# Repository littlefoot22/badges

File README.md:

# Char badge

https://twitter.com/littlefoot20_2/status/1213898357694971907/photo/1
https://twitter.com/littlefoot20_2/status/1128459009160359936/photo/1

# Dolly badge

https://twitter.com/littlefoot20_2/status/1213898357694971907/photo/2
https://twitter.com/littlefoot20_2/status/1159295666331553794?s=21

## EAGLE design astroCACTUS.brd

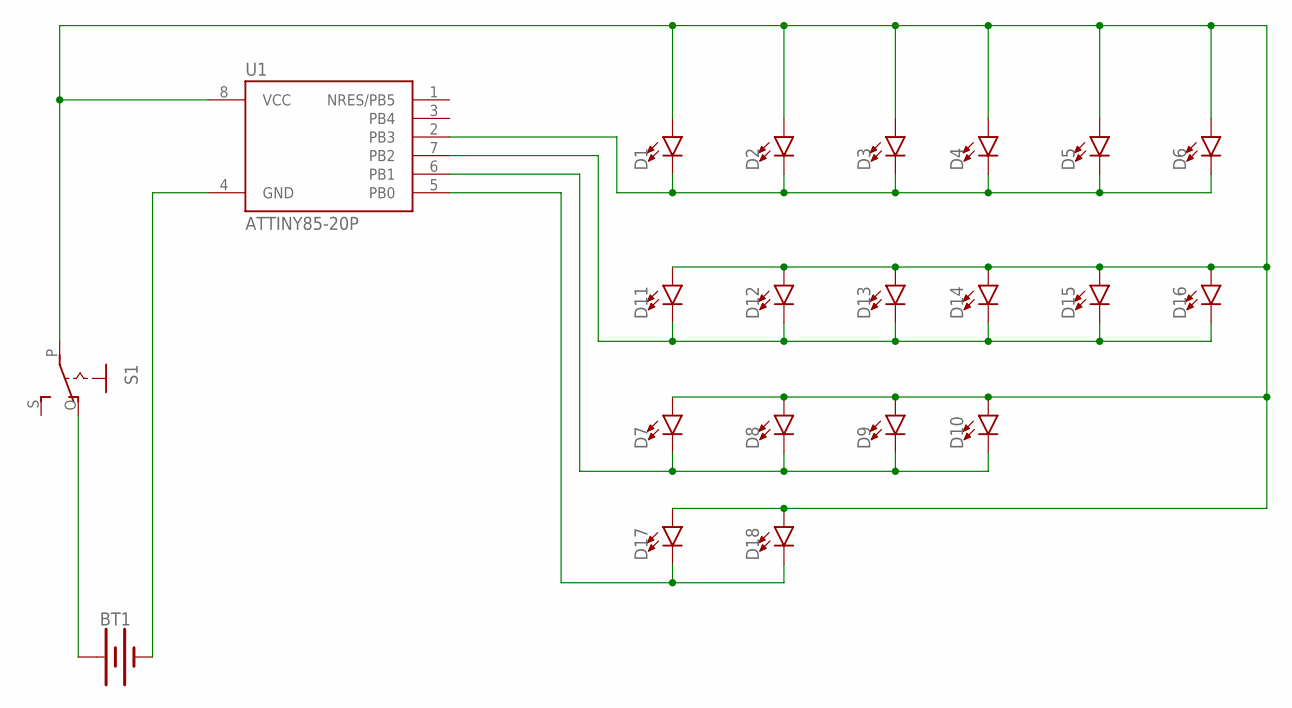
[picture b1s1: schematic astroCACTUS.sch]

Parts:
BT1: BATTERY-20MM_PTH; BATTCOM_20MM_PTH
D1, D2, D3, D4, D5, D6, D7, D8, D9, D10, D11, D12, D13, D14, D15, D16, D17, D18: LED3MM; LED_3MM
S1: EG1218S; EG1218
U1: ATTINY85-20P; PDIP08_300MIL

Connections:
unnamed: D1.K (C), D2.K (C), D3.K (C), D4.K (C), D5.K (C), D6.K (C), U1.2 (PB3)
unnamed: BT1.1 (+), S1.O
unnamed: D11.K (C), D12.K (C), D13.K (C), D14.K (C), D15.K (C), D16.K (C), U1.7 (PB2)
unnamed: D7.K (C), D8.K (C), D9.K (C), D10.K (C), U1.6 (PB1)
unnamed: BT1.2 (-), U1.4 (GND)
unnamed: D17.K (C), D18.K (C), U1.5 (PB0)
unnamed: D1.A, D2.A, D3.A, D4.A, D5.A, D6.A, D7.A, D8.A, D9.A, D10.A, D11.A, D12.A, D13.A, D14.A, D15.A, D16.A, D17.A, D18.A, S1.P, U1.8 (VCC)

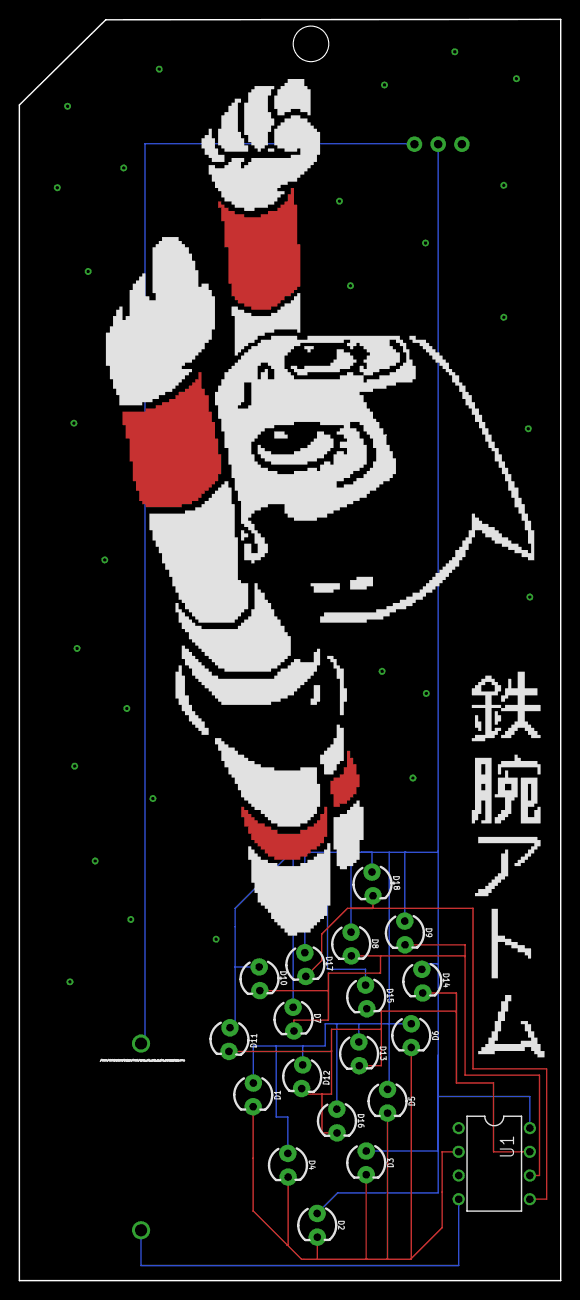
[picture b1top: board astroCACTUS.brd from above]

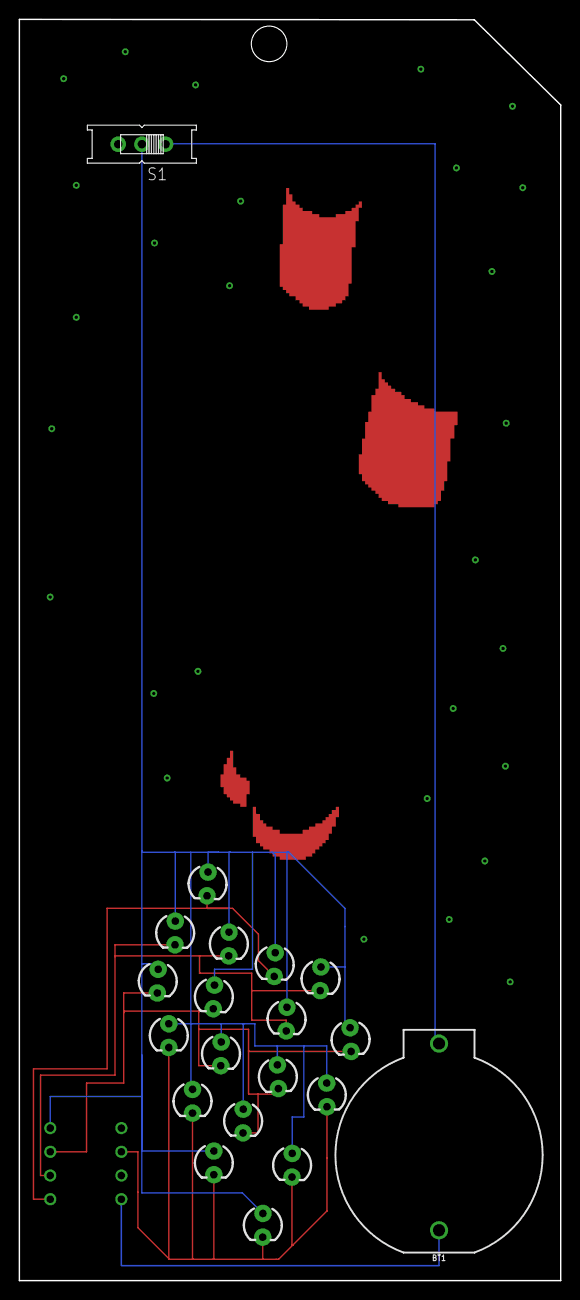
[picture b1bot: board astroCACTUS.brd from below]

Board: 2 copper layers, 58.0 x 135.1 mm, 21 parts (2 on the bottom side), 7 nets.

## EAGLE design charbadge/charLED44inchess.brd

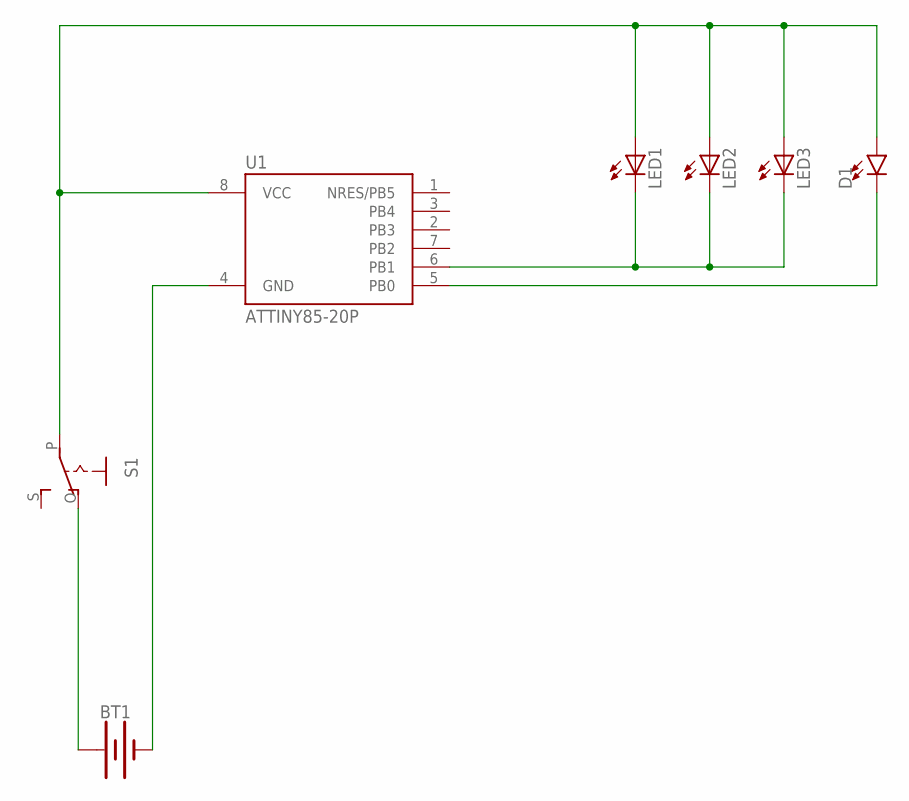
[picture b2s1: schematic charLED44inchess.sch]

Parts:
BT1: BATTERY-20MM_PTH; BATTCOM_20MM_PTH
D1: LED3MM; LED_3MM
LED1, LED2, LED3: LED5MM
S1: EG1218S; EG1218
U1: ATTINY85-20P; PDIP08_300MIL

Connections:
unnamed: LED1.K (C), LED2.K (C), LED3.K (C), U1.6 (PB1)
unnamed: BT1.1 (+), S1.O
unnamed: D1.K (C), U1.5 (PB0)
unnamed: BT1.2 (-), U1.4 (GND)
unnamed: D1.A, LED1.A, LED2.A, LED3.A, S1.P, U1.8 (VCC)

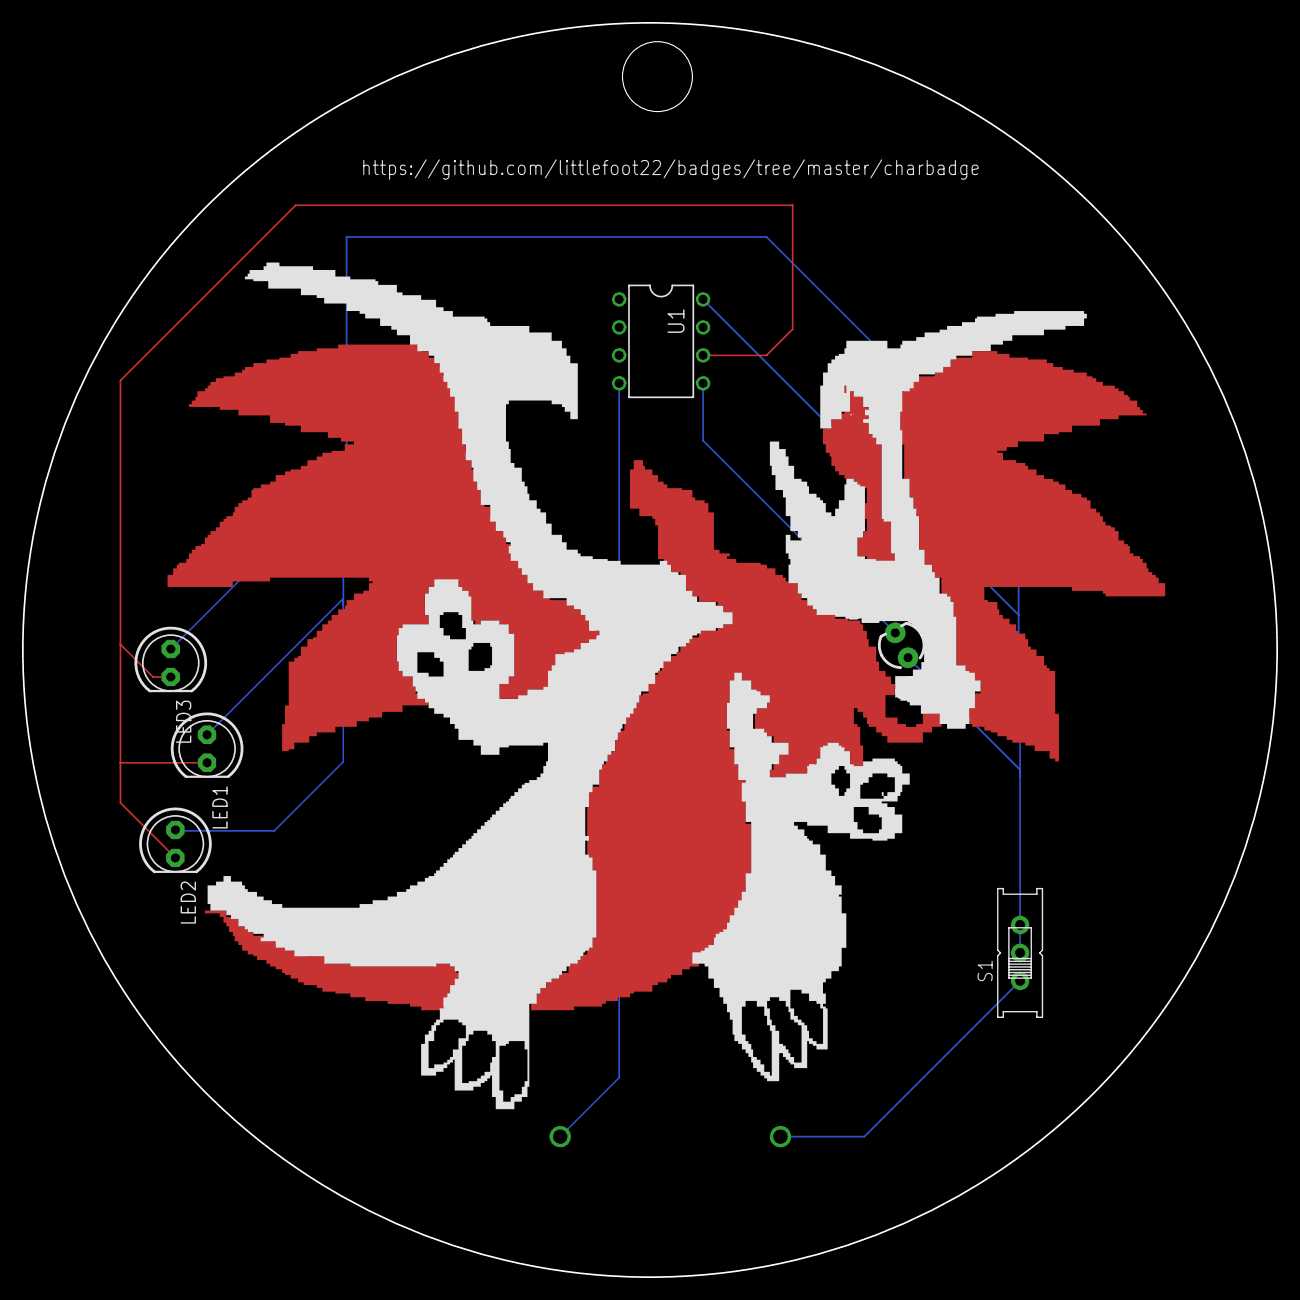
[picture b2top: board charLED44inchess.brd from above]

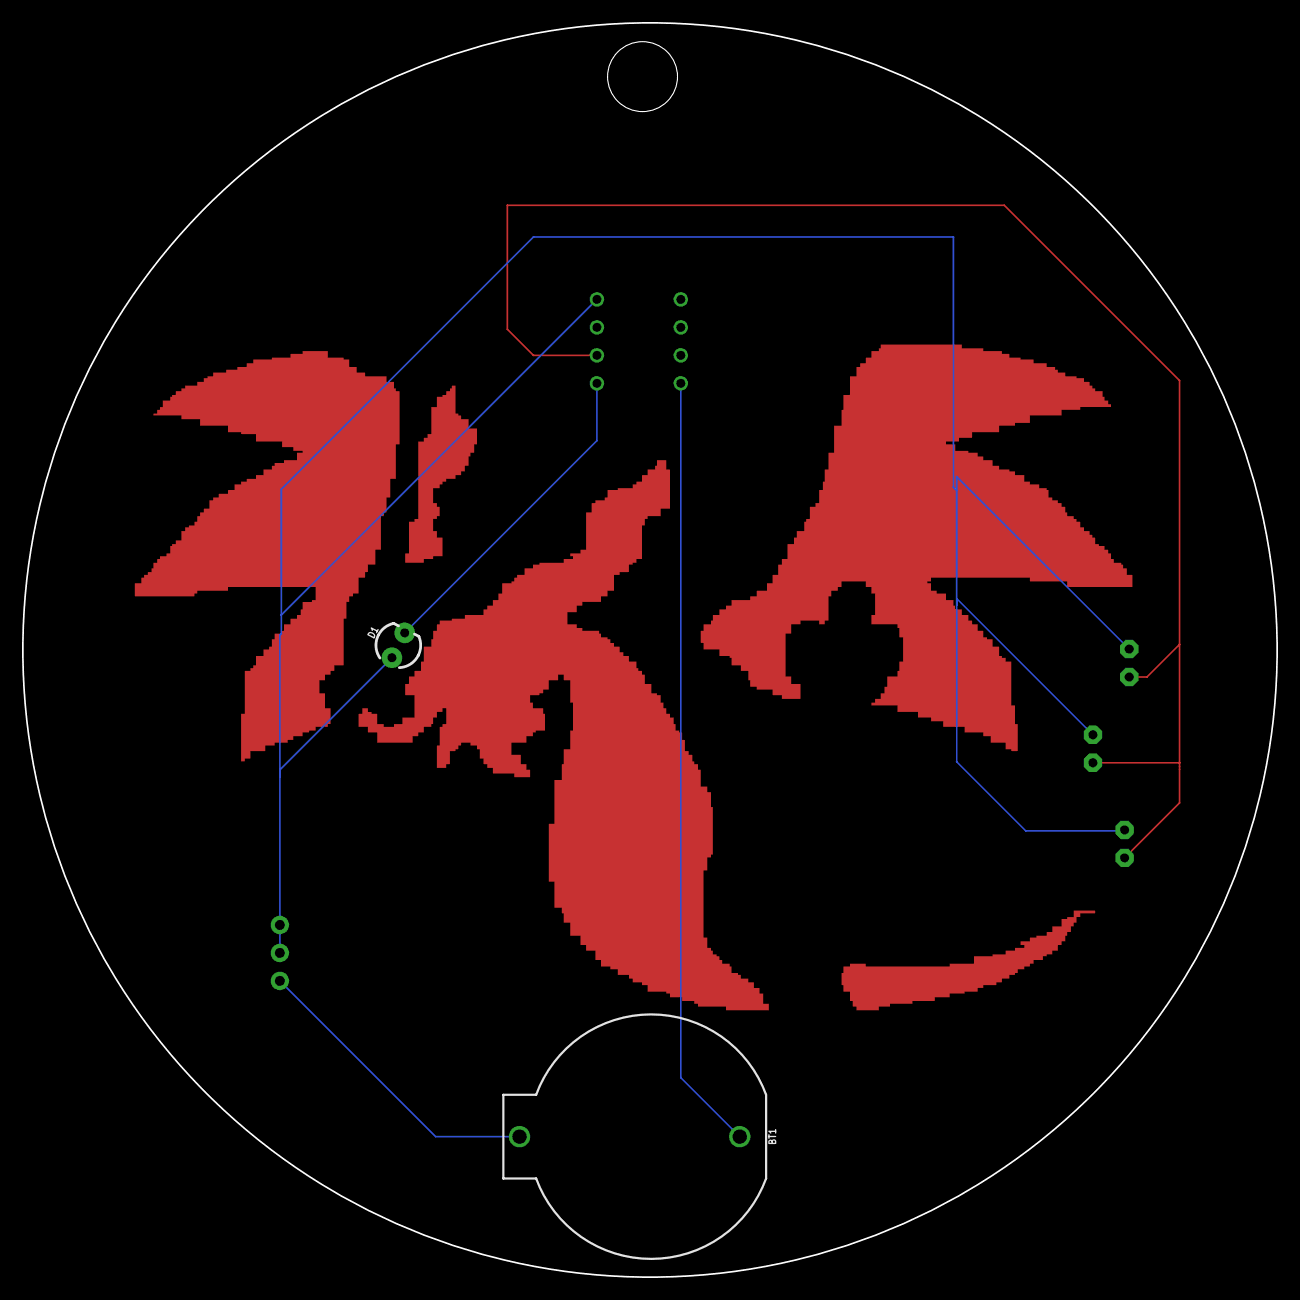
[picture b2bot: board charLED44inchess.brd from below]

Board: 2 copper layers, 113.9 x 113.9 mm, 7 parts (2 on the bottom side), 5 nets.

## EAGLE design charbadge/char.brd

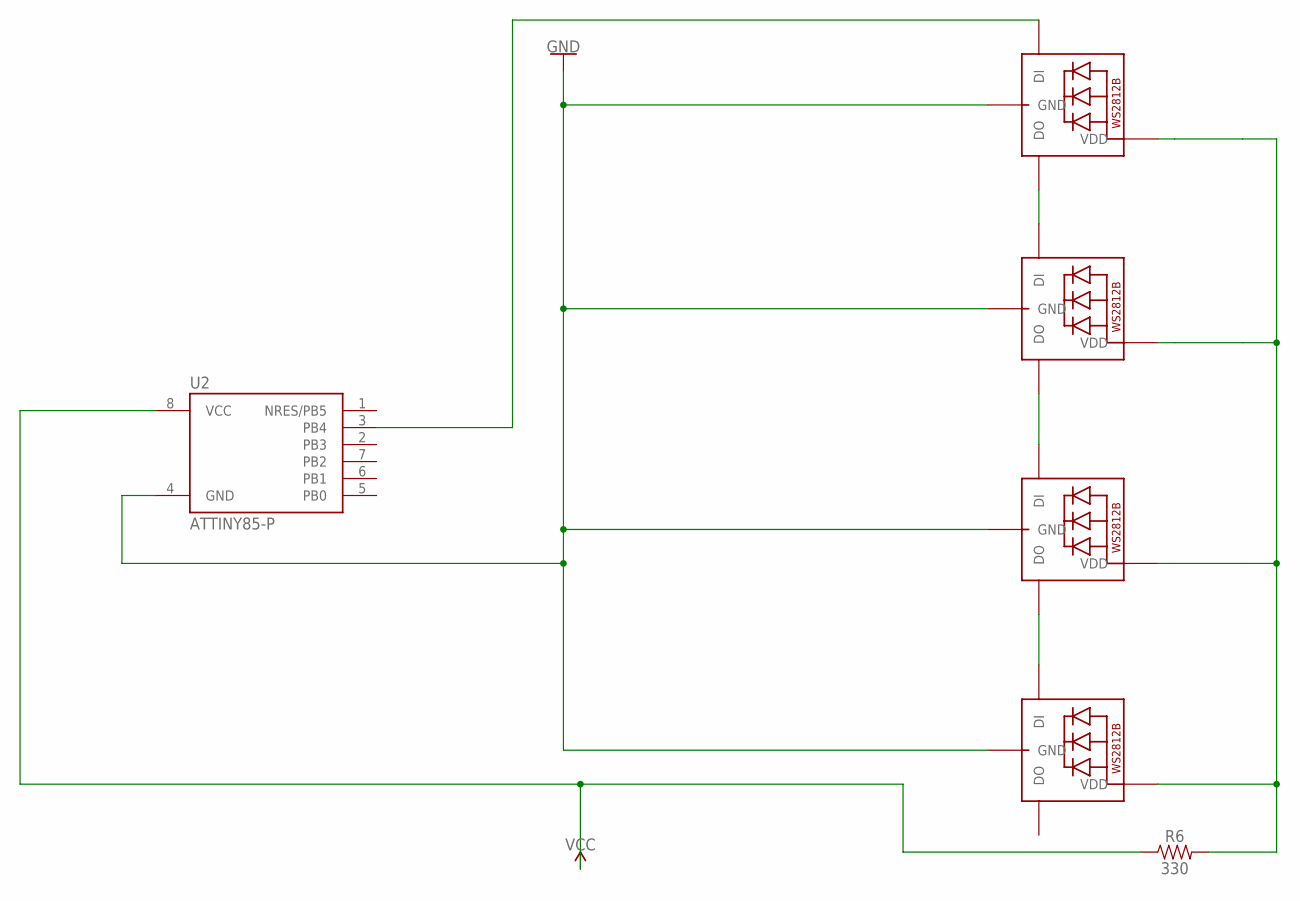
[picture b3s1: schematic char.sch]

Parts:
R6: 330; AXIAL-0.3
U2: ATTINY85-P; PDIP08_300MIL
U$1, U$2, U$3, U$4: THROHOLE; LED5MMRGB

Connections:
GND: U2.4 (GND), U$1.2 (GND), U$2.2 (GND), U$3.2 (GND), U$4.2 (GND)
unnamed: U2.3 (PB4), U$4.1 (DI)
unnamed: U$1.1 (DI), U$4.4 (DO)
unnamed: U$1.4 (DO), U$2.1 (DI)
unnamed: U$2.4 (DO), U$3.1 (DI)
unnamed: R6.P$2 (2), U$1.3 (VDD), U$2.3 (VDD), U$3.3 (VDD), U$4.3 (VDD)
VCC: R6.P$1 (1), U2.8 (VCC)

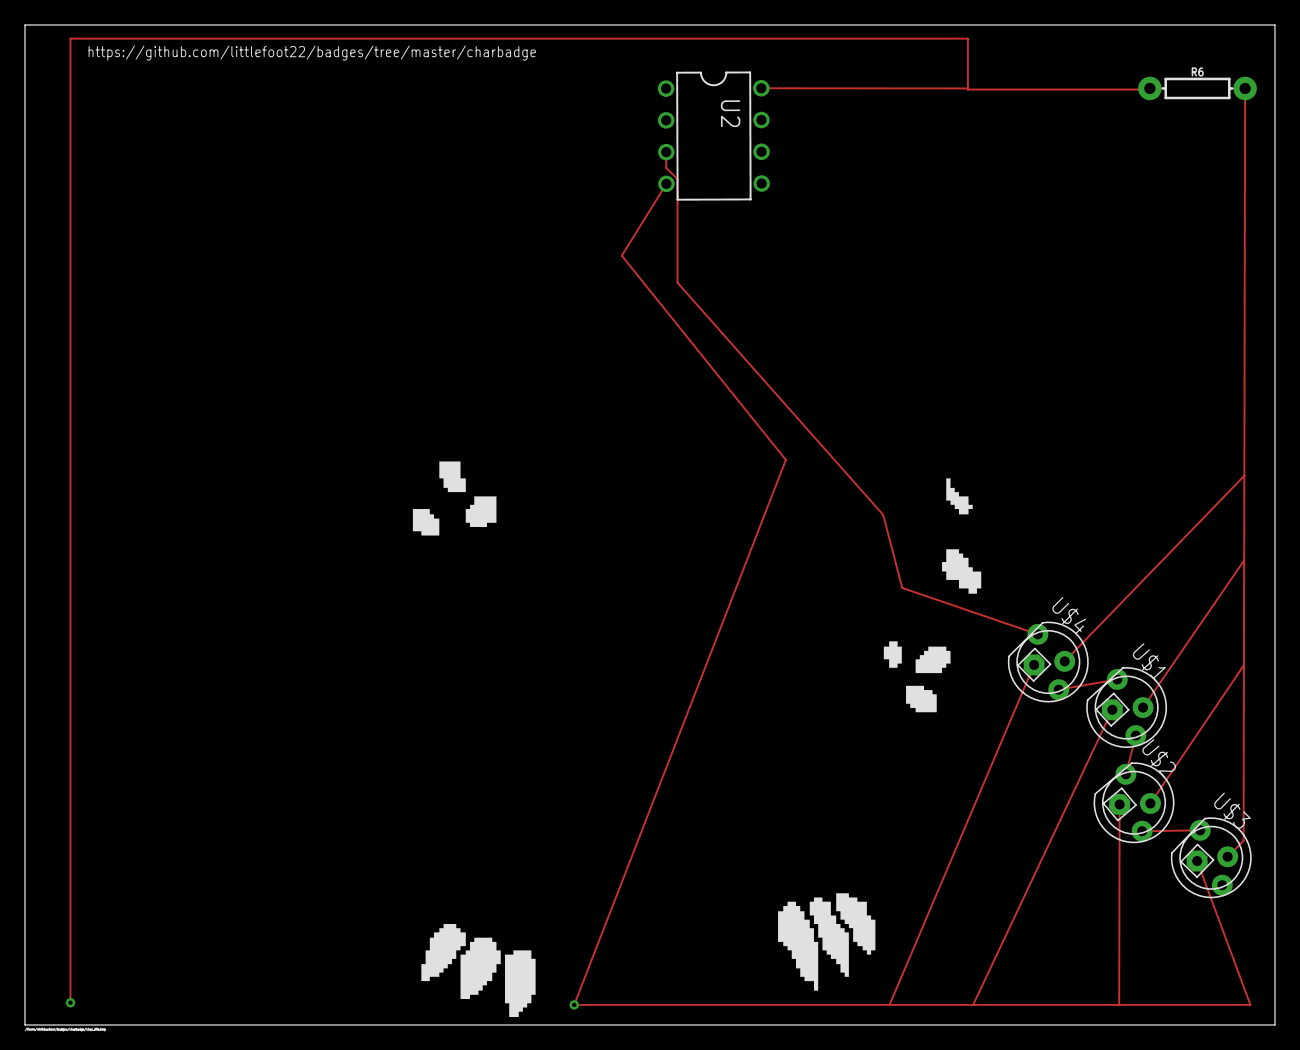
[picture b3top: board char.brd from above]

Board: 2 copper layers, 100.0 x 80.0 mm, 6 parts (0 on the bottom side), 7 nets.

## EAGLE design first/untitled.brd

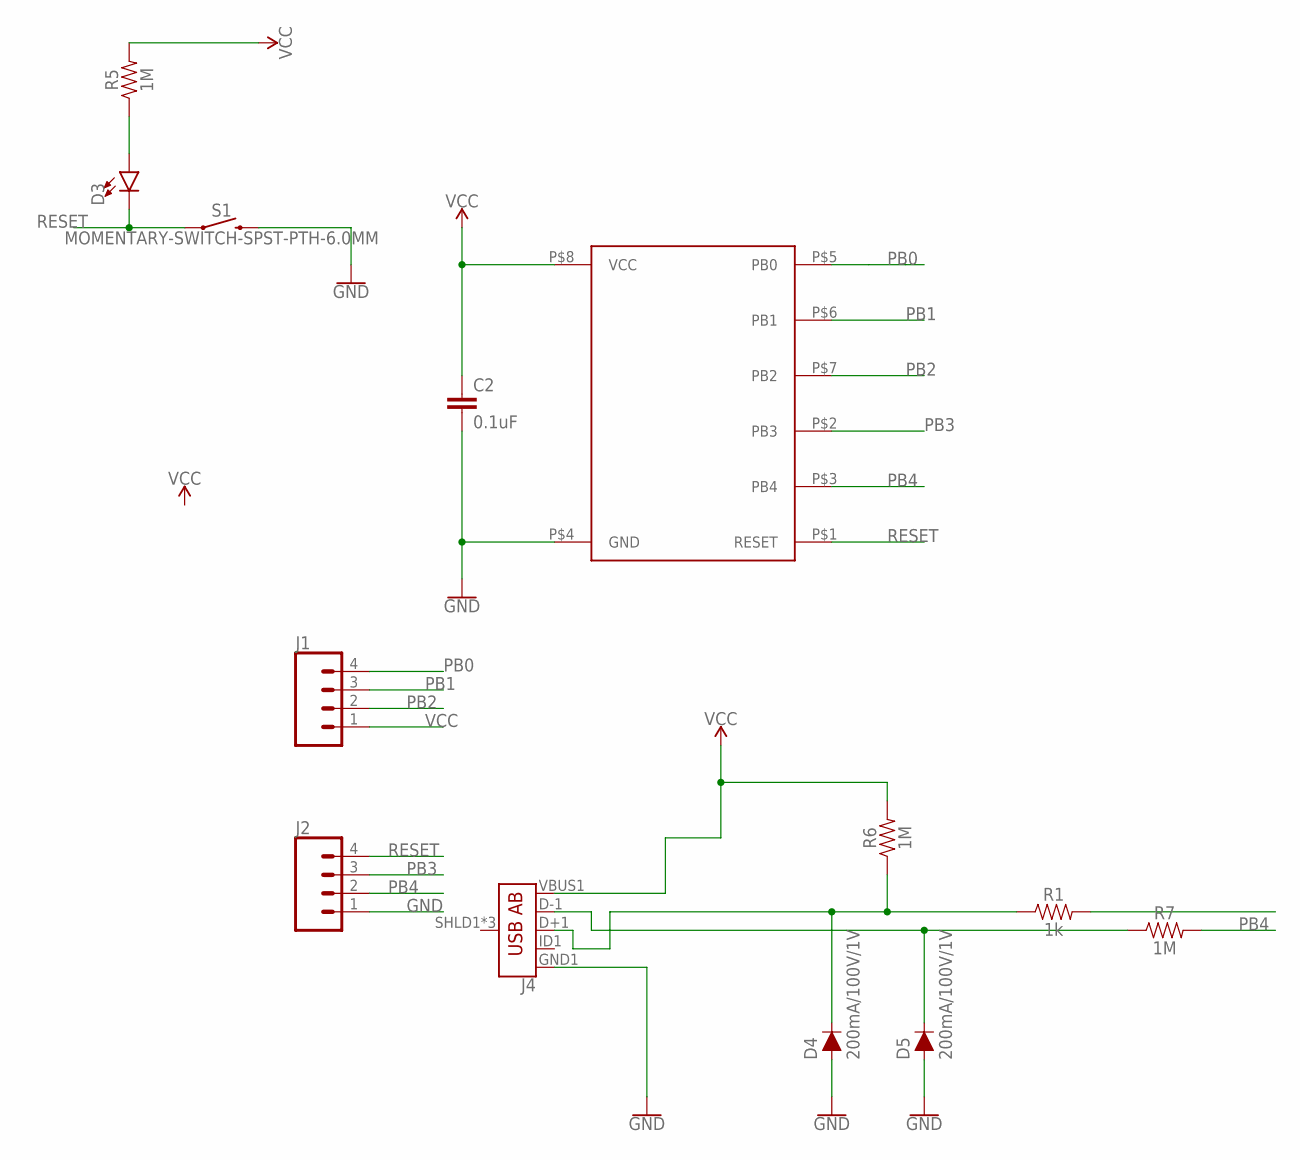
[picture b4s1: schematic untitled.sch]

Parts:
C2: 0.1uF; CAP-PTH-SMALL-KIT
D3: LED-3MM-NO_SILK; LED_3MM-NS
D4, D5: 200mA/100V/1V; DIODE-1N4148
J1, J2: CONN_04; 1X04
J4: USB_AB_SMT; USB-AB-MICRO-SMD
R1: 1k; AXIAL-0.3
R5, R6, R7: 1M; AXIAL-0.3
S1: MOMENTARY-SWITCH-SPST-PTH-6.0MM; TACTILE_SWITCH_PTH_6.0MM
U$2: ATINY85; DIP8

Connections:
GND: C2.2, D4.A, D5.A, J2.1, J4.GND1 (GND), S1.3 (2), U$2.P$4 (GND)
unnamed: D3.A, R5.P$1 (1)
unnamed: D5.C, J4.D-1 (D-), R7.P$1 (1)
unnamed: D4.C, J4.D+1 (D+), R1.P$1 (1), R6.P$1 (1)
PB0: J1.4, U$2.P$5 (PB0)
PB1: J1.3, U$2.P$6 (PB1)
PB2: J1.2, U$2.P$7 (PB2)
PB3: J2.3, R1.P$2 (2), U$2.P$2 (PB3)
PB4: J2.2, R7.P$2 (2), U$2.P$3 (PB4)
RESET: D3.K (C), J2.4, S1.1, U$2.P$1 (RESET)
VCC: C2.1, J1.1, J4.VBUS1 (VBUS), R5.P$2 (2), R6.P$2 (2), U$2.P$8 (VCC)

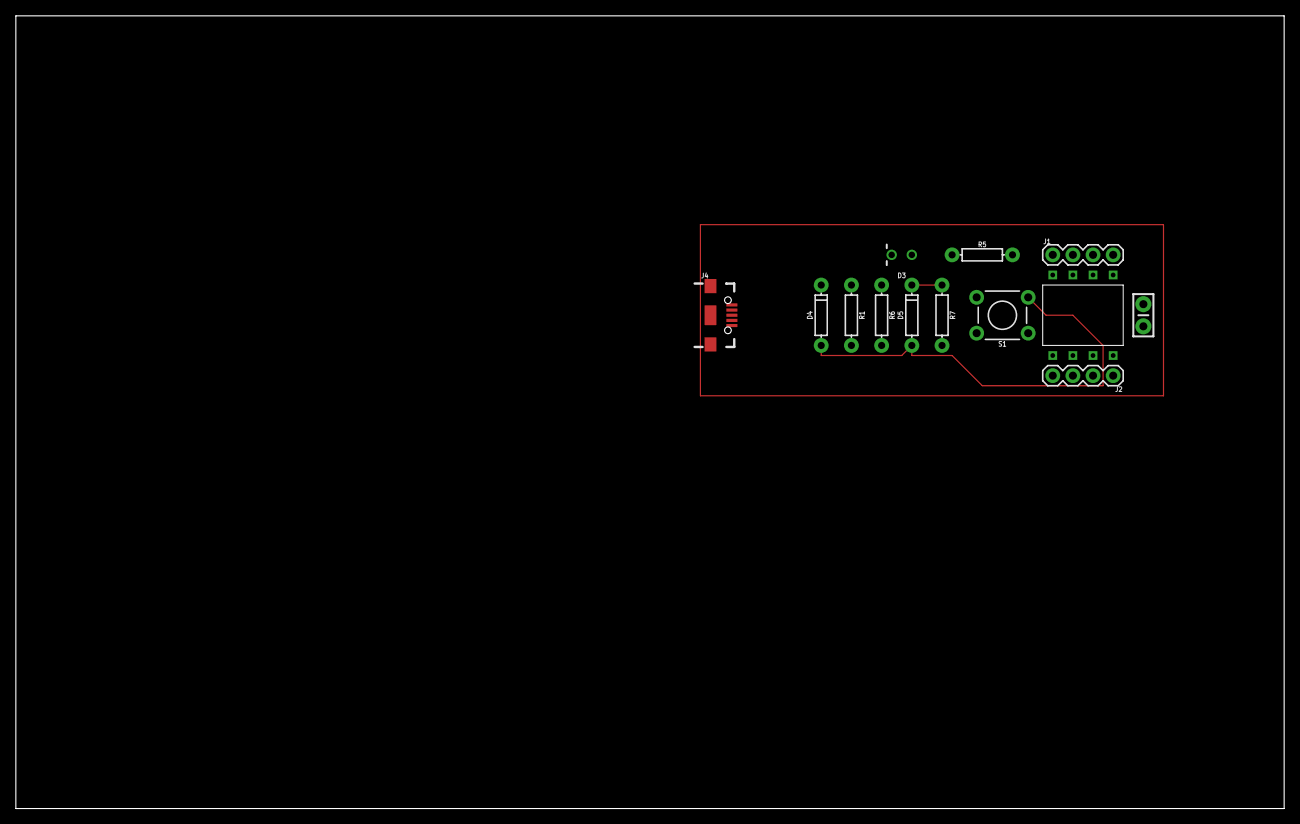
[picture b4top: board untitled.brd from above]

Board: 2 copper layers, 160.0 x 100.0 mm, 13 parts (0 on the bottom side), 11 nets.

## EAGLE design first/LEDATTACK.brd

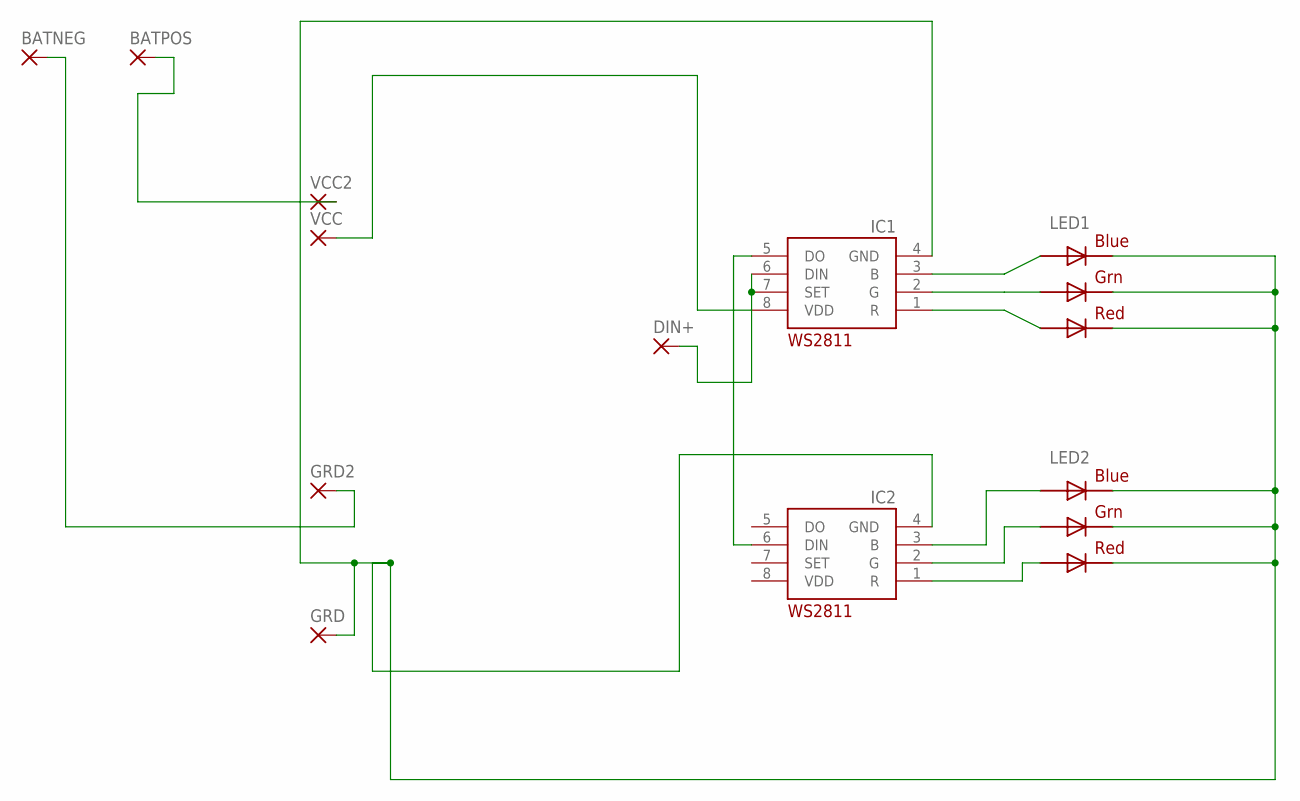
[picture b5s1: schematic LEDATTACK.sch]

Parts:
BATNEG: 1,6/0,8
BATPOS: 1,6/0,8
DIN+: 1,6/0,8
GRD, GRD2: 1,6/0,8
IC1, IC2: WS2811-SOP8; SO08-SKINNYPADS
LED1, LED2: RGBLED5050
VCC, VCC2: 1,6/0,8

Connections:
unnamed: IC1.3 (B), LED1.3 (BLUE_A)
unnamed: IC1.2 (G), LED1.1 (GREEN_A)
unnamed: IC1.1 (R), LED1.2 (RED_A)
unnamed: GRD.1, IC1.4 (GND), IC2.4 (GND), LED1.4 (BLUE_C), LED1.5 (RED_C), LED1.6 (GREEN_C), LED2.4 (BLUE_C), LED2.5 (RED_C), LED2.6 (GREEN_C)
unnamed: IC1.8 (VDD), VCC.1
unnamed: DIN+.1, IC1.6 (DIN), IC1.7 (SET)
unnamed: IC1.5 (DO), IC2.6 (DIN)
unnamed: IC2.1 (R), LED2.2 (RED_A)
unnamed: IC2.2 (G), LED2.1 (GREEN_A)
unnamed: IC2.3 (B), LED2.3 (BLUE_A)
unnamed: BATPOS.1, VCC2.1
unnamed: BATNEG.1, GRD2.1
VDD: IC2.8 (VDD)

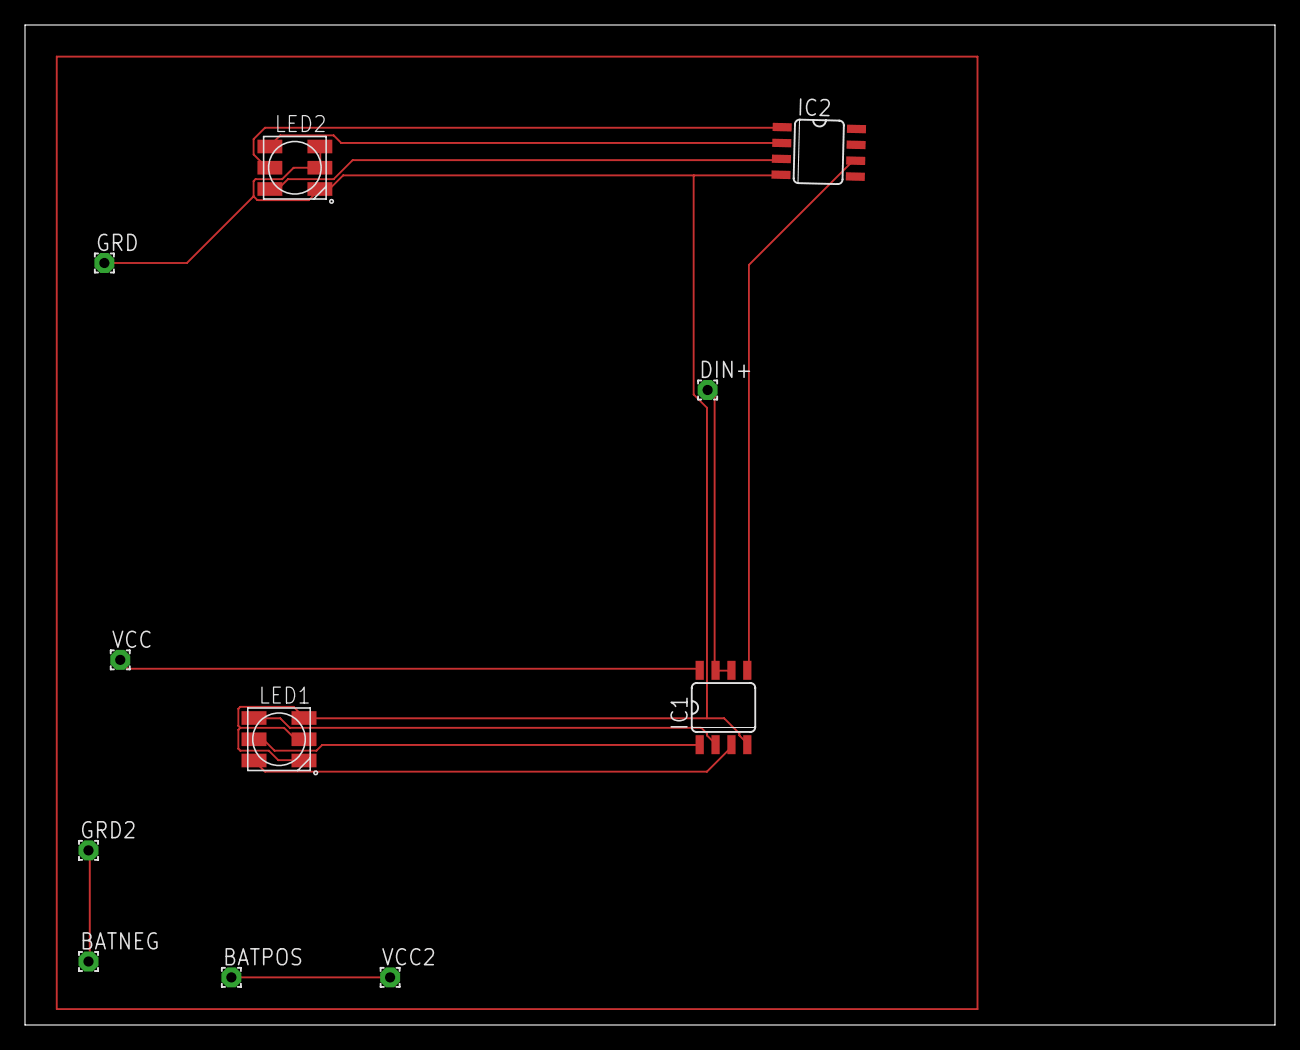
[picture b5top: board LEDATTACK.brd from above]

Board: 2 copper layers, 100.0 x 80.0 mm, 11 parts (0 on the bottom side), 12 nets.

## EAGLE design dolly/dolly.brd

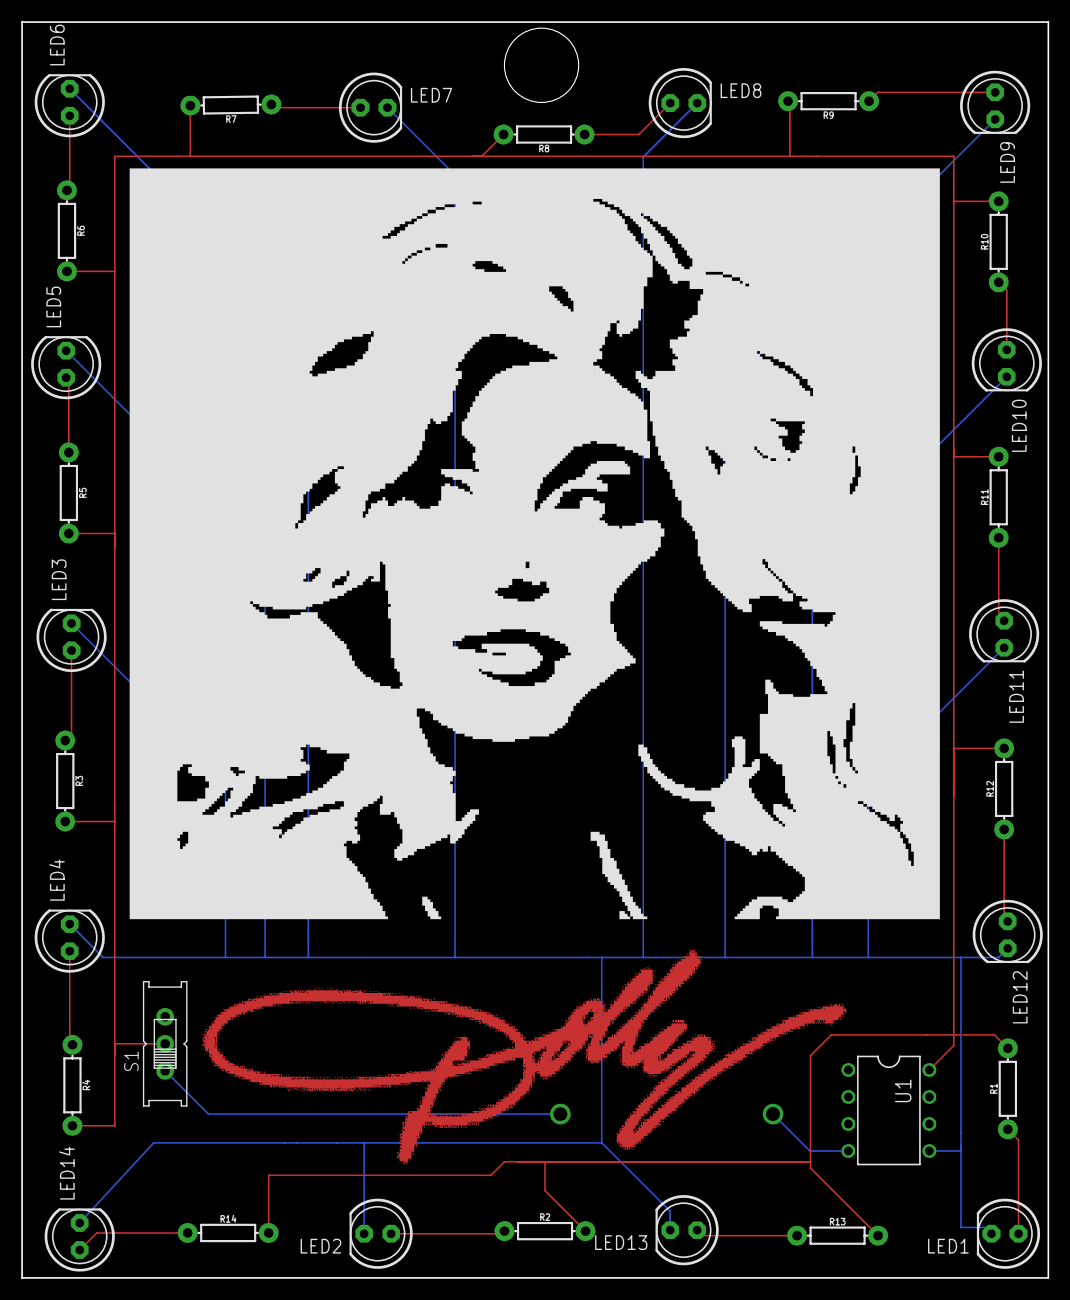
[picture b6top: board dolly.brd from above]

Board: 2 copper layers, 96.5 x 118.1 mm, 31 parts (1 on the bottom side), 18 nets.

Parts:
BT1: BATTCOM_20MM_PTH
LED1, LED2, LED3, LED4, LED5, LED6, LED7, LED8, LED9, LED10, LED11, LED12, LED13, LED14: LED5MM
R1, R2, R3, R4, R5, R6, R7, R8, R9, R10, R11, R12, R13, R14: 10k; AXIAL-0.3
S1: EG1218
U1: ATTINY85-20P; PDIP08_300MIL

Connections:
unnamed: LED1.A, R1.P$1
unnamed: BT1.1, S1.O
unnamed: LED3.A, R3.P$1
unnamed: LED1.K, LED2.K, LED3.K, LED4.K, LED5.K, LED6.K, LED7.K, LED8.K, LED9.K, LED10.K, LED11.K, LED12.K, LED13.K, LED14.K, U1.5
unnamed: BT1.2, U1.4
unnamed: R1.P$2, R2.P$2, R3.P$2, R4.P$2, R5.P$2, R6.P$2, R7.P$2, R8.P$2, R9.P$2, R10.P$2, R11.P$2, R12.P$2, R13.P$2, R14.P$2, S1.P, U1.8
unnamed: LED4.A, R4.P$1
unnamed: LED5.A, R5.P$1
unnamed: LED6.A, R6.P$1
unnamed: LED7.A, R7.P$1
unnamed: LED8.A, R8.P$1
unnamed: LED9.A, R9.P$1
unnamed: LED10.A, R10.P$1
unnamed: LED11.A, R11.P$1
unnamed: LED12.A, R12.P$1
unnamed: LED13.A, R13.P$1
unnamed: LED14.A, R14.P$1
unnamed: LED2.A, R2.P$1

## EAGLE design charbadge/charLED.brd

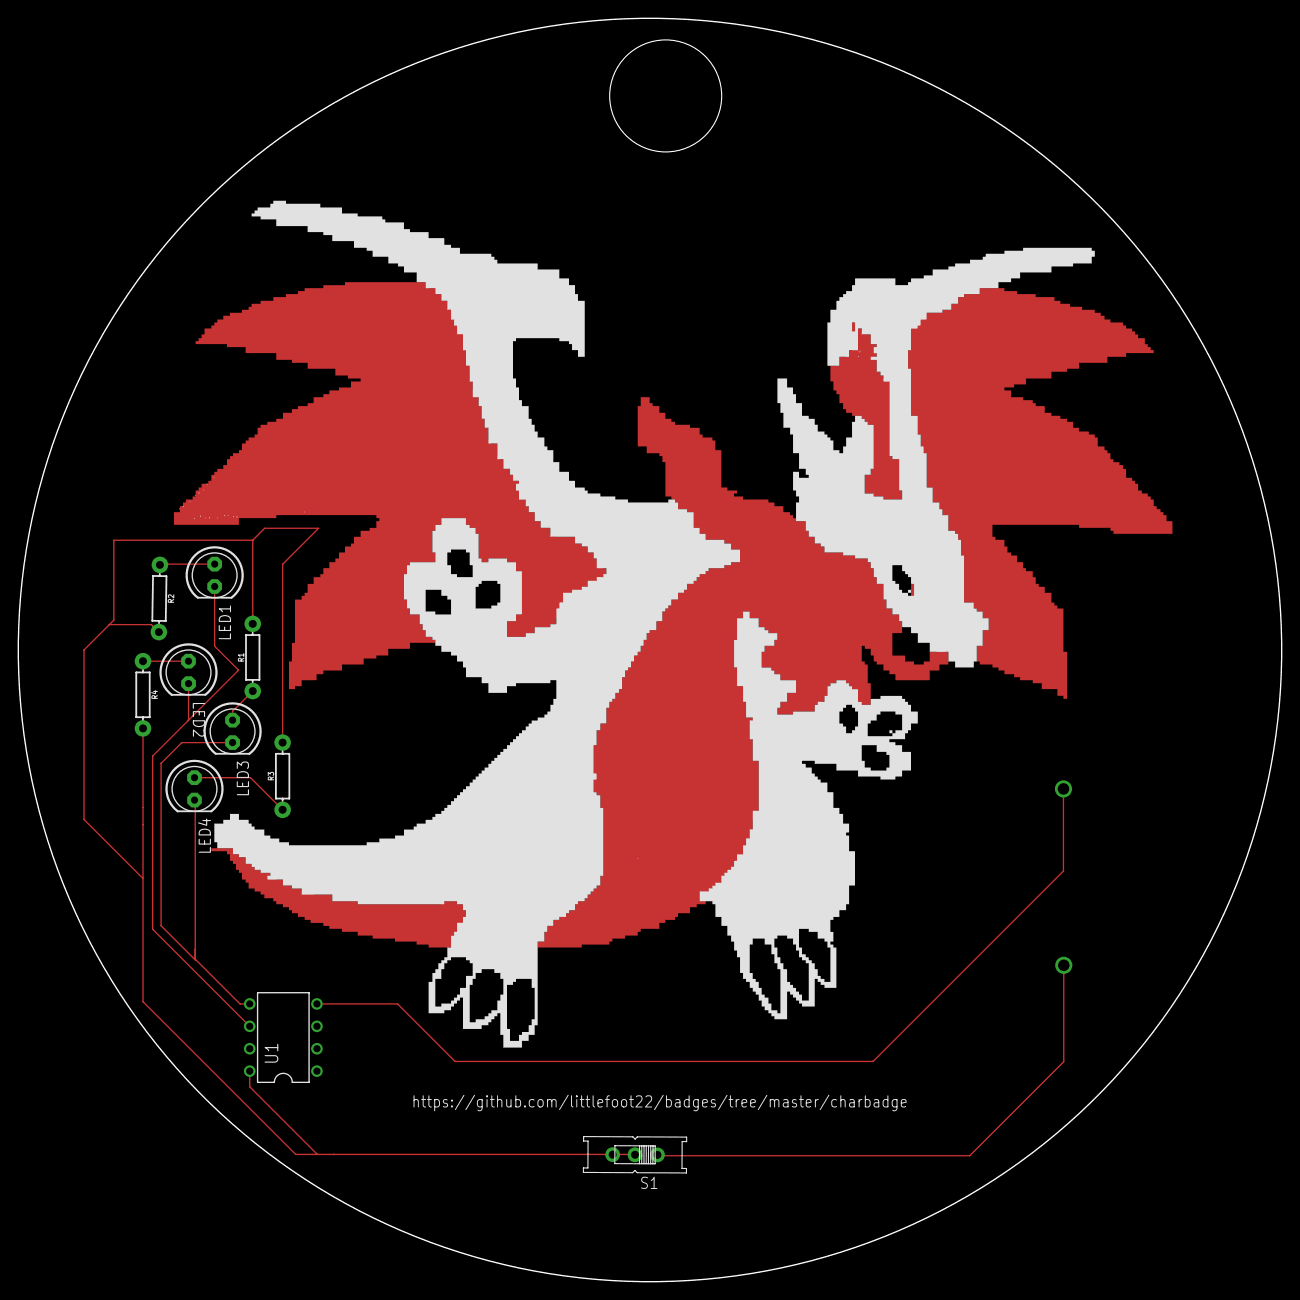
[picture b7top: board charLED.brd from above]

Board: 2 copper layers, 143.2 x 143.2 mm, 11 parts (1 on the bottom side), 9 nets.

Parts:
BT1: BATTCOM_20MM_PTH
LED1, LED2, LED3, LED4: LED5MM
R1, R2, R3, R4: 100k; AXIAL-0.3
S1: EG1218
U1: ATTINY85-20P; PDIP08_300MIL

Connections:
unnamed: LED1.K, LED2.K, U1.6
unnamed: LED1.A, R2.P$1
unnamed: BT1.2, S1.O
unnamed: LED3.K, LED4.K, U1.5
unnamed: BT1.1, U1.4
unnamed: R1.P$2, R2.P$2, R3.P$2, R4.P$2, S1.P, U1.8
unnamed: LED2.A, R4.P$1
unnamed: LED4.A, R3.P$1
unnamed: LED3.A, R1.P$1

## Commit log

2018-08-15 fileS
2018-09-04 badges
2018-11-04 LED attack
2019-02-12 ps file for char badge
2019-02-13 outlins for char badge
2019-02-15 char badge
2019-02-17 cahr badge
2019-04-05 charrr badgeee
2019-06-06 DOLLY BADGE OK LOL
2019-06-26 resize dolly badge
2019-07-21 dolly badge
2020-01-07 fresh prince
2020-01-10 applestore.py
2020-01-14 astro boy

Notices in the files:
parts and their libraries:
SparkFun-Batteries: Licensing: Creative Commons ShareAlike 4.0 International - https://creativecommons.org/licenses/by-sa/4.0
